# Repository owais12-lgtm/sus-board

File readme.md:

# About
This is a RP2040 based Pi Pico clone thats in the shape of an among us character. 
# features
- Dual-core M0+ processor
- Flexible clock running up to 133 MHz
- 264 kB of SRAM
- USB 1.1 controller and PHY with device and host support
- Low-power sleep and dormant modes
- Accurate clock and timer
- Accelerated floating-point libraries
- Temperature sensor
- Eight Programmable I/O (PIO) state machines for custom peripheral support
# PCB

# SCHEMATIC

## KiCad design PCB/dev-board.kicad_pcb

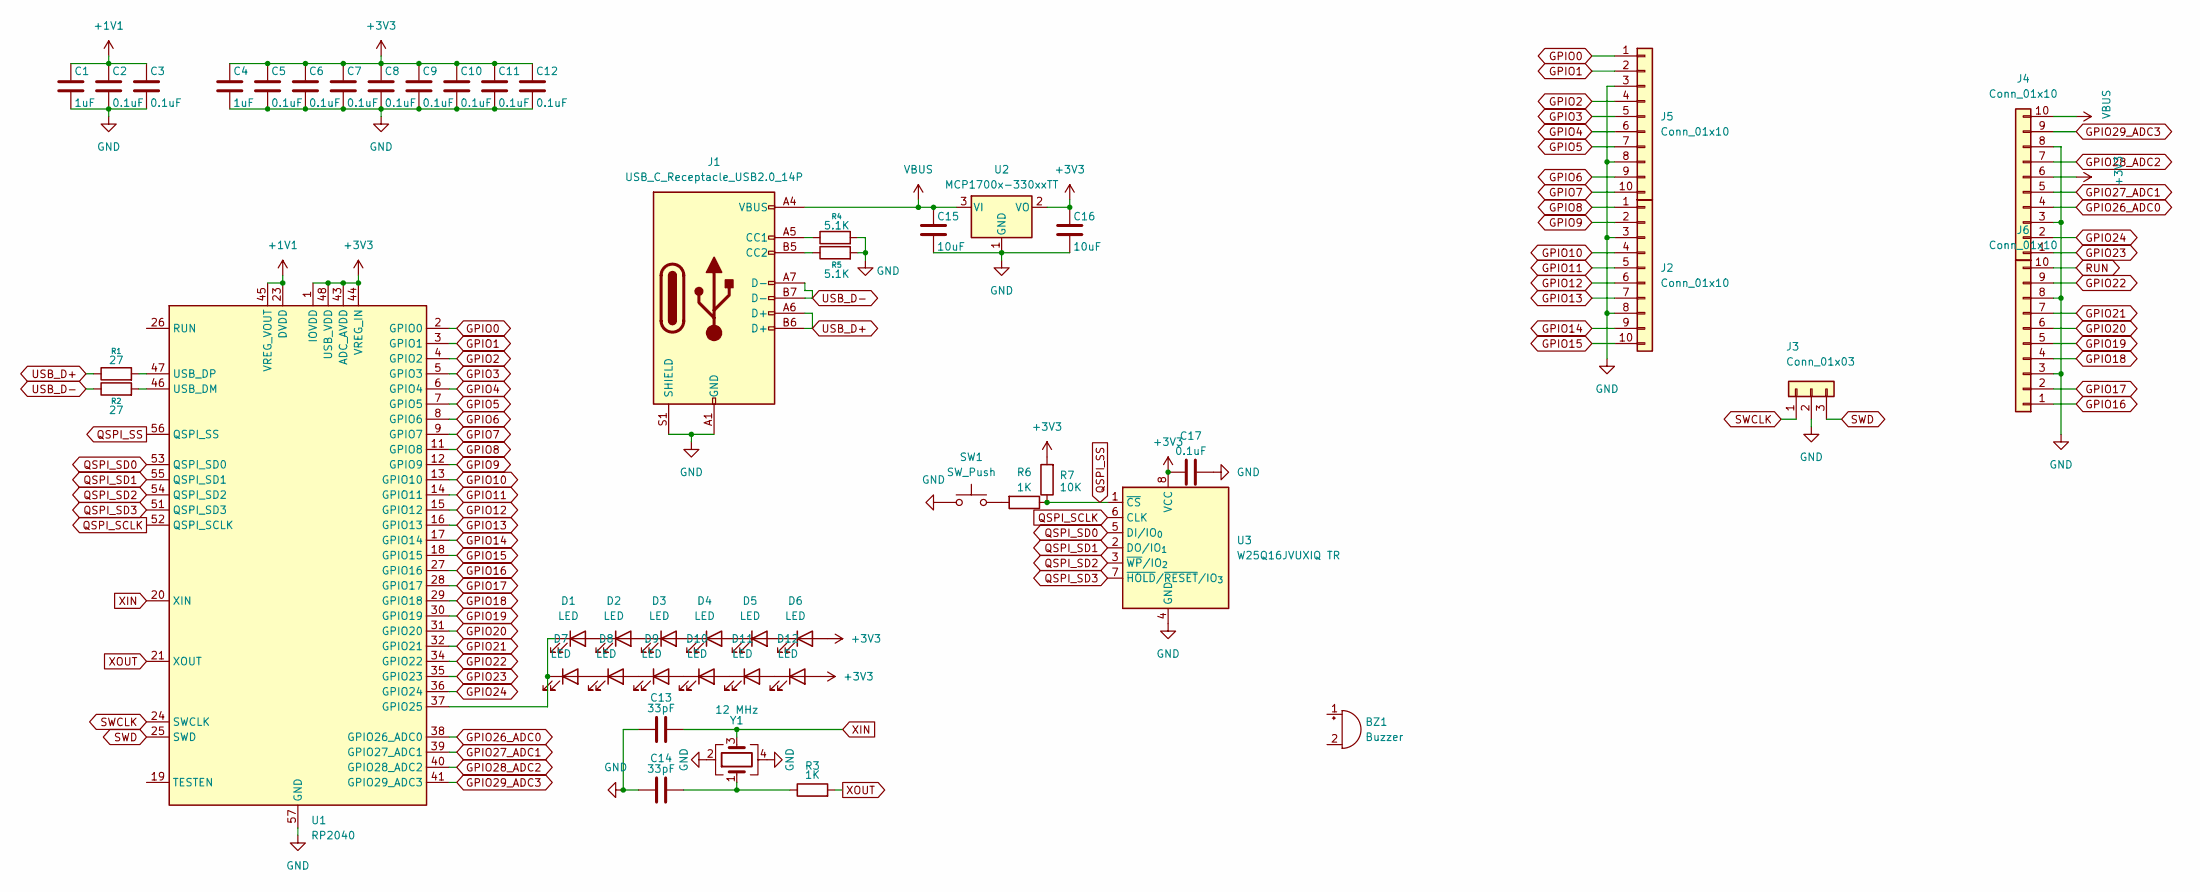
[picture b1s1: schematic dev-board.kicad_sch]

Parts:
BZ1: Buzzer; Buzzer_CUI_CPT-9019S-SMT
C1, C4: 1uF; C_0402_1005Metric
C2, C3, C5, C6, C7, C8, C9, C10, C11, C12, C17: 0.1uF; C_0402_1005Metric
C13, C14: 33pF; C_0402_1005Metric
C15, C16: 10uF; C_0603_1608Metric
D1, D2, D3, D4, D5, D6, D7, D8, D9, D10, D11, D12: LED; LED_0201_0603Metric
J1: USB_C_Receptacle_USB2.0_14P; USB_C_Receptacle_HRO_TYPE-C-31-M-12
J2, J4, J5, J6: Conn_01x10; PinHeader_1x10_P2.54mm_Vertical
J3: Conn_01x03; PinHeader_1x03_P2.54mm_Vertical
R1, R2: 27; R_0402_1005Metric
R3, R6: 1K; R_0402_1005Metric
R4, R5: 5.1K; R_0402_1005Metric
R7: 10K; R_0402_1005Metric
SW1: SW_Push; SW_Push_SPST_NO_Alps_SKRK
U1: RP2040; QFN-56-1EP_7x7mm_P0.4mm_EP3.2x3.2mm
U2: MCP1700x-330xxTT; SOT-23
U3: W25Q16JVUXIQ TR; Winbond_USON-8-1EP_3x2mm_P0.5mm_EP0.2x1.6mm
Y1: 12 MHz; Crystal_SMD_3225-4Pin_3.2x2.5mm

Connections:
+1V1: C1.1, C2.1, C3.1, U1.23 (DVDD), U1.45 (VREG_VOUT), U1.50 (DVDD)
+3V3: C4.1, C5.1, C6.1, C7.1, C8.1, C9.1, C10.1, C11.1, C12.1, C16.1, C17.1, D6.2 (A), D12.2 (A), J4.6, R7.2, U1.1 (IOVDD), U1.10 (IOVDD), U1.22 (IOVDD), U1.33 (IOVDD), U1.42 (IOVDD), U1.43 (ADC_AVDD), U1.44 (VREG_IN), U1.48 (USB_VDD), U1.49 (IOVDD), U2.2 (VO), U3.8 (VCC)
GND: C1.2, C2.2, C3.2, C4.2, C5.2, C6.2, C7.2, C8.2, C9.2, C10.2, C11.2, C12.2, C13.1, C14.1, C15.2, C16.2, C17.2, J1.A1 (GND), J1.A12 (GND), J1.B1 (GND), J1.B12 (GND), J1.S1 (SHIELD), J2.3, J2.8, J3.2, J4.3, J4.8, J5.3, J5.8, J6.3, J6.8, R4.2, R5.2, SW1.1, U1.57 (GND), U2.1 (GND), U3.4 (GND), Y1.2, Y1.4
GPIO0: J5.1, U1.2 (GPIO0)
GPIO1: J5.2, U1.3 (GPIO1)
GPIO2: J5.4, U1.4 (GPIO2)
GPIO3: J5.5, U1.5 (GPIO3)
GPIO4: J5.6, U1.6 (GPIO4)
GPIO5: J5.7, U1.7 (GPIO5)
GPIO6: J5.9, U1.8 (GPIO6)
GPIO7: J5.10, U1.9 (GPIO7)
GPIO8: J2.1, U1.11 (GPIO8)
GPIO9: J2.2, U1.12 (GPIO9)
GPIO10: J2.4, U1.13 (GPIO10)
GPIO11: J2.5, U1.14 (GPIO11)
GPIO12: J2.6, U1.15 (GPIO12)
GPIO13: J2.7, U1.16 (GPIO13)
GPIO14: J2.9, U1.17 (GPIO14)
GPIO15: J2.10, U1.18 (GPIO15)
GPIO16: J6.1, U1.27 (GPIO16)
GPIO17: J6.2, U1.28 (GPIO17)
GPIO18: J6.4, U1.29 (GPIO18)
GPIO19: J6.5, U1.30 (GPIO19)
GPIO20: J6.6, U1.31 (GPIO20)
GPIO21: J6.7, U1.32 (GPIO21)
GPIO22: J6.9, U1.34 (GPIO22)
GPIO23: J4.1, U1.35 (GPIO23)
GPIO24: J4.2, U1.36 (GPIO24)
GPIO26_ADC0: J4.4, U1.38 (GPIO26_ADC0)
GPIO27_ADC1: J4.5, U1.39 (GPIO27_ADC1)
GPIO28_ADC2: J4.7, U1.40 (GPIO28_ADC2)
GPIO29_ADC3: J4.9, U1.41 (GPIO29_ADC3)
unnamed: C14.2, R3.1, Y1.1
unnamed: D1.2 (A), D2.1 (K)
unnamed: D1.1 (K), D7.1 (K), U1.37 (GPIO25)
unnamed: D2.2 (A), D3.1 (K)
unnamed: D3.2 (A), D4.1 (K)
unnamed: D4.2 (A), D5.1 (K)
unnamed: D5.2 (A), D6.1 (K)
unnamed: D7.2 (A), D8.1 (K)
unnamed: D8.2 (A), D9.1 (K)
unnamed: D10.2 (A), D11.1 (K)
unnamed: D9.2 (A), D10.1 (K)
unnamed: D11.2 (A), D12.1 (K)
unnamed: J1.A5 (CC1), R4.1
unnamed: J1.B5 (CC2), R5.1
unnamed: R6.2, SW1.2
unnamed: R2.2, U1.46 (USB_DM)
unnamed: R1.2, U1.47 (USB_DP)
QSPI_SCLK: U1.52 (QSPI_SCLK), U3.6 (CLK)
QSPI_SD0: U1.53 (QSPI_SD0), U3.5 (DI/IO_{0})
QSPI_SD1: U1.55 (QSPI_SD1), U3.2 (DO/IO_{1})
QSPI_SD2: U1.54 (QSPI_SD2), U3.3 (~WP/IO_{2})
QSPI_SD3: U1.51 (QSPI_SD3), U3.7 (~HOLD/~RESET/IO_{3})
QSPI_SS: R6.1, R7.1, U1.56 (QSPI_SS), U3.1 (~CS)
RUN: J6.10
SWCLK: J3.1, U1.24 (SWCLK)
SWD: J3.3, U1.25 (SWD)
USB_D+: J1.A6 (D+), J1.B6 (D+), R1.1
USB_D-: J1.A7 (D-), J1.B7 (D-), R2.1
VBUS: C15.1, J1.A4 (VBUS), J1.A9 (VBUS), J1.B4 (VBUS), J1.B9 (VBUS), J4.10, U2.3 (VI)
XIN: C13.2, U1.20 (XIN), Y1.3
XOUT: R3.2, U1.21 (XOUT)

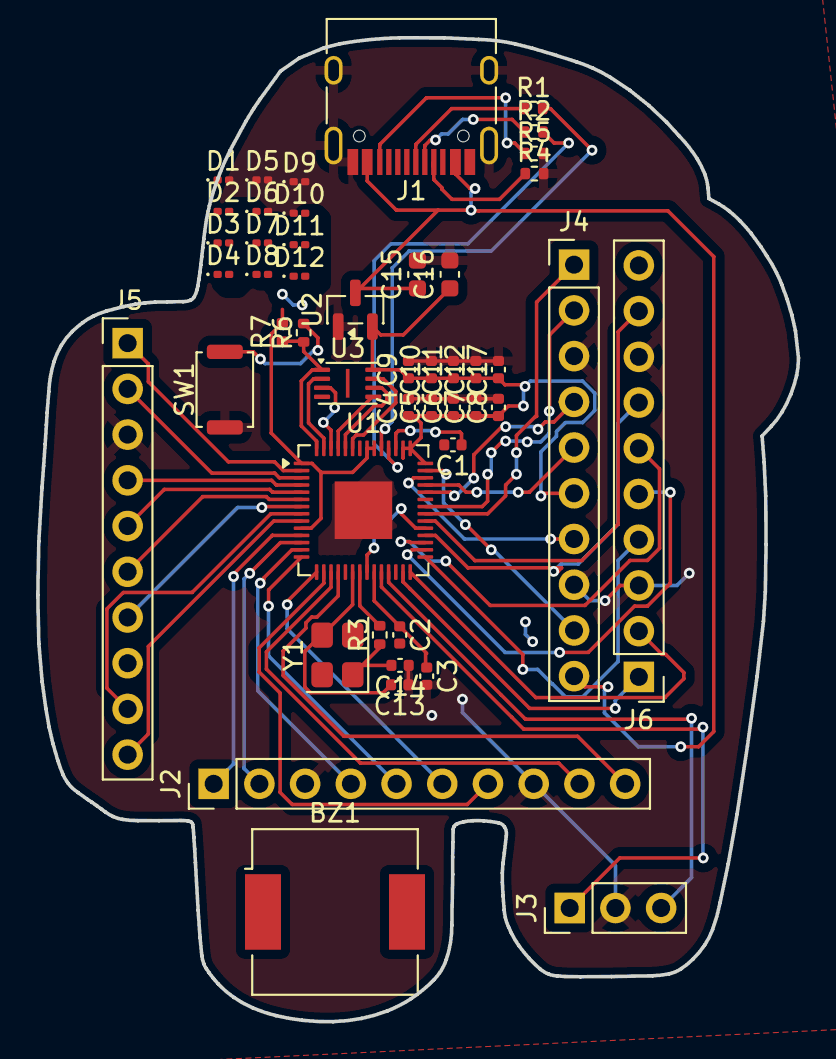
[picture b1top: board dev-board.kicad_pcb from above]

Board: 2 copper layers, 42.3 x 54.7 mm, 48 parts (0 on the bottom side), 62 nets.

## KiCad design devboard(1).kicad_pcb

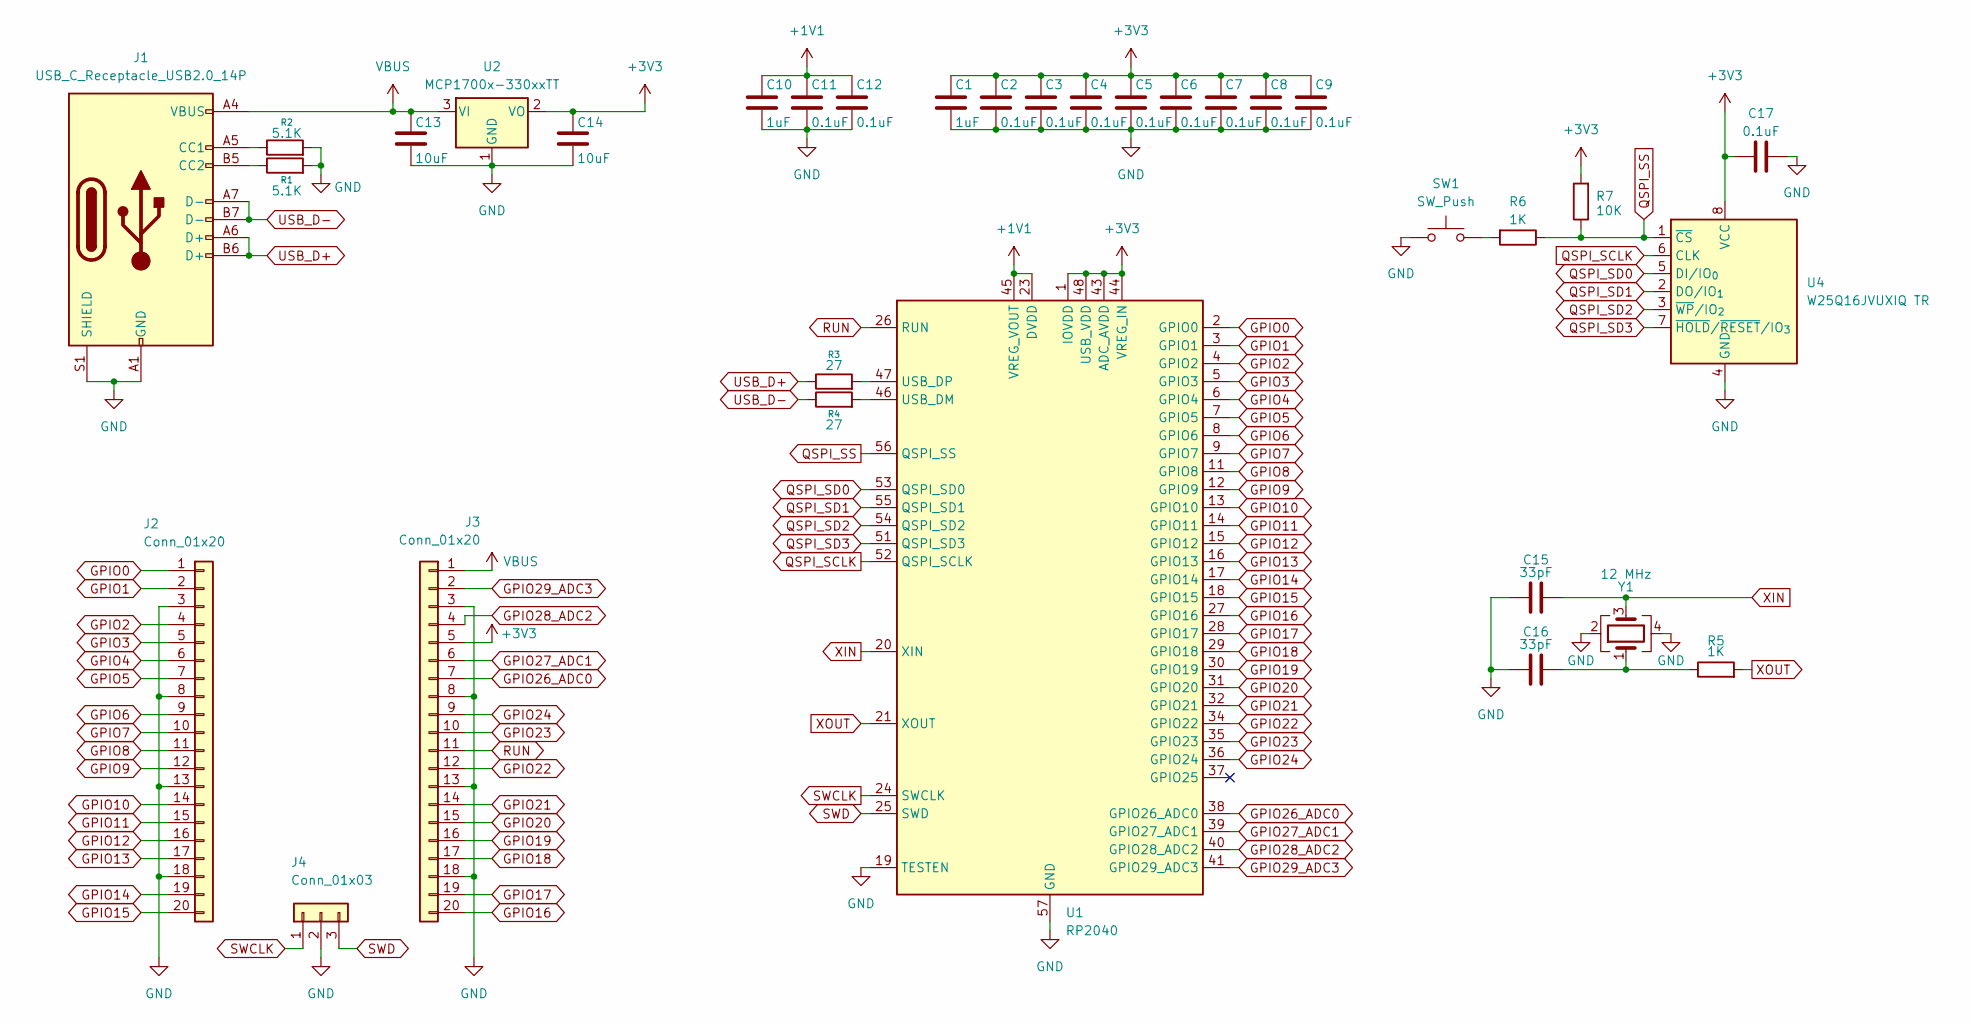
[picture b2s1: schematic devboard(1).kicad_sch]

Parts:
C1, C10: 1uF; C_0402_1005Metric
C2, C3, C4, C5, C6, C7, C8, C9, C11, C12, C17: 0.1uF; C_0402_1005Metric
C13, C14: 10uF; C_0603_1608Metric
C15, C16: 33pF; C_0402_1005Metric
J1: USB_C_Receptacle_USB2.0_14P; USB_C_Receptacle_HRO_TYPE-C-31-M-12
J2, J3: Conn_01x20; PinHeader_1x20_P2.54mm_Vertical
J4: Conn_01x03; PinHeader_1x03_P2.54mm_Vertical
R1, R2: 5.1K; R_0402_1005Metric
R3, R4: 27; R_0402_1005Metric
R5, R6: 1K; R_0402_1005Metric
R7: 10K; R_0402_1005Metric
SW1: SW_Push; SW_Push_SPST_NO_Alps_SKRK
U1: RP2040; QFN-56-1EP_7x7mm_P0.4mm_EP3.2x3.2mm
U2: MCP1700x-330xxTT; SOT-23
U4: W25Q16JVUXIQ TR; Winbond_USON-8-1EP_3x2mm_P0.5mm_EP0.2x1.6mm
Y1: 12 MHz; Crystal_SMD_3225-4Pin_3.2x2.5mm

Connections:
+1V1: C10.1, C11.1, C12.1, U1.23 (DVDD), U1.45 (VREG_VOUT), U1.50 (DVDD)
+3V3: C1.1, C2.1, C3.1, C4.1, C5.1, C6.1, C7.1, C8.1, C9.1, C14.1, C17.1, J3.5, R7.2, U1.1 (IOVDD), U1.10 (IOVDD), U1.22 (IOVDD), U1.33 (IOVDD), U1.42 (IOVDD), U1.43 (ADC_AVDD), U1.44 (VREG_IN), U1.48 (USB_VDD), U1.49 (IOVDD), U2.2 (VO), U4.8 (VCC)
GND: C1.2, C2.2, C3.2, C4.2, C5.2, C6.2, C7.2, C8.2, C9.2, C10.2, C11.2, C12.2, C13.2, C14.2, C15.1, C16.1, C17.2, J1.A1 (GND), J1.A12 (GND), J1.B1 (GND), J1.B12 (GND), J1.S1 (SHIELD), J2.3, J2.8, J2.13, J2.18, J3.3, J3.8, J3.13, J3.18, J4.2, R1.2, R2.2, SW1.1, U1.19 (TESTEN), U1.57 (GND), U2.1 (GND), U4.4 (GND), Y1.2, Y1.4
GPIO0: J2.1, U1.2 (GPIO0)
GPIO1: J2.2, U1.3 (GPIO1)
GPIO2: J2.4, U1.4 (GPIO2)
GPIO3: J2.5, U1.5 (GPIO3)
GPIO4: J2.6, U1.6 (GPIO4)
GPIO5: J2.7, U1.7 (GPIO5)
GPIO6: J2.9, U1.8 (GPIO6)
GPIO7: J2.10, U1.9 (GPIO7)
GPIO8: J2.11, U1.11 (GPIO8)
GPIO9: J2.12, U1.12 (GPIO9)
GPIO10: J2.14, U1.13 (GPIO10)
GPIO11: J2.15, U1.14 (GPIO11)
GPIO12: J2.16, U1.15 (GPIO12)
GPIO13: J2.17, U1.16 (GPIO13)
GPIO14: J2.19, U1.17 (GPIO14)
GPIO15: J2.20, U1.18 (GPIO15)
GPIO16: J3.20, U1.27 (GPIO16)
GPIO17: J3.19, U1.28 (GPIO17)
GPIO18: J3.17, U1.29 (GPIO18)
GPIO19: J3.16, U1.30 (GPIO19)
GPIO20: J3.15, U1.31 (GPIO20)
GPIO21: J3.14, U1.32 (GPIO21)
GPIO22: J3.12, U1.34 (GPIO22)
GPIO23: J3.10, U1.35 (GPIO23)
GPIO24: J3.9, U1.36 (GPIO24)
GPIO26_ADC0: J3.7, U1.38 (GPIO26_ADC0)
GPIO27_ADC1: J3.6, U1.39 (GPIO27_ADC1)
GPIO28_ADC2: J3.4, U1.40 (GPIO28_ADC2)
GPIO29_ADC3: J3.2, U1.41 (GPIO29_ADC3)
unnamed: C16.2, R5.1, Y1.1
unnamed: J1.A5 (CC1), R2.1
unnamed: J1.B5 (CC2), R1.1
unnamed: R6.2, SW1.2
unnamed: R4.2, U1.46 (USB_DM)
unnamed: R3.2, U1.47 (USB_DP)
QSPI_SCLK: U1.52 (QSPI_SCLK), U4.6 (CLK)
QSPI_SD0: U1.53 (QSPI_SD0), U4.5 (DI/IO_{0})
QSPI_SD1: U1.55 (QSPI_SD1), U4.2 (DO/IO_{1})
QSPI_SD2: U1.54 (QSPI_SD2), U4.3 (~WP/IO_{2})
QSPI_SD3: U1.51 (QSPI_SD3), U4.7 (~HOLD/~RESET/IO_{3})
QSPI_SS: R6.1, R7.1, U1.56 (QSPI_SS), U4.1 (~CS)
RUN: J3.11, U1.26 (RUN)
SWCLK: J4.1, U1.24 (SWCLK)
SWD: J4.3, U1.25 (SWD)
USB_D+: J1.A6 (D+), J1.B6 (D+), R3.1
USB_D-: J1.A7 (D-), J1.B7 (D-), R4.1
VBUS: C13.1, J1.A4 (VBUS), J1.A9 (VBUS), J1.B4 (VBUS), J1.B9 (VBUS), J3.1, U2.3 (VI)
XIN: C15.2, U1.20 (XIN), Y1.3
XOUT: R5.2, U1.21 (XOUT)

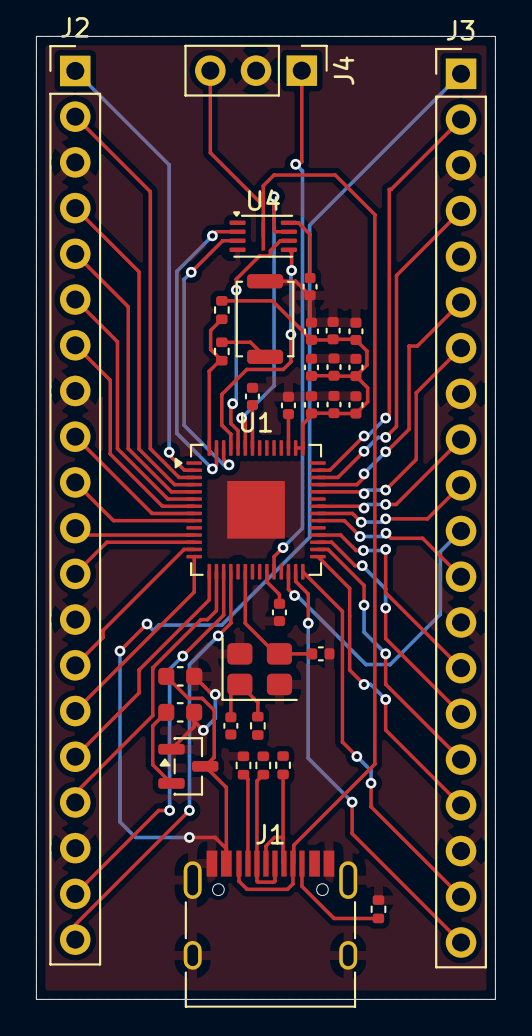
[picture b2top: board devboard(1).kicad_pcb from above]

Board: 2 copper layers, 25.5 x 53.5 mm, 33 parts (0 on the bottom side), 52 nets.
